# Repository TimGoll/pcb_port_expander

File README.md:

# SPI Port Expander - MCP23S17

library: https://github.com/MajenkoLibraries/MCP23S17

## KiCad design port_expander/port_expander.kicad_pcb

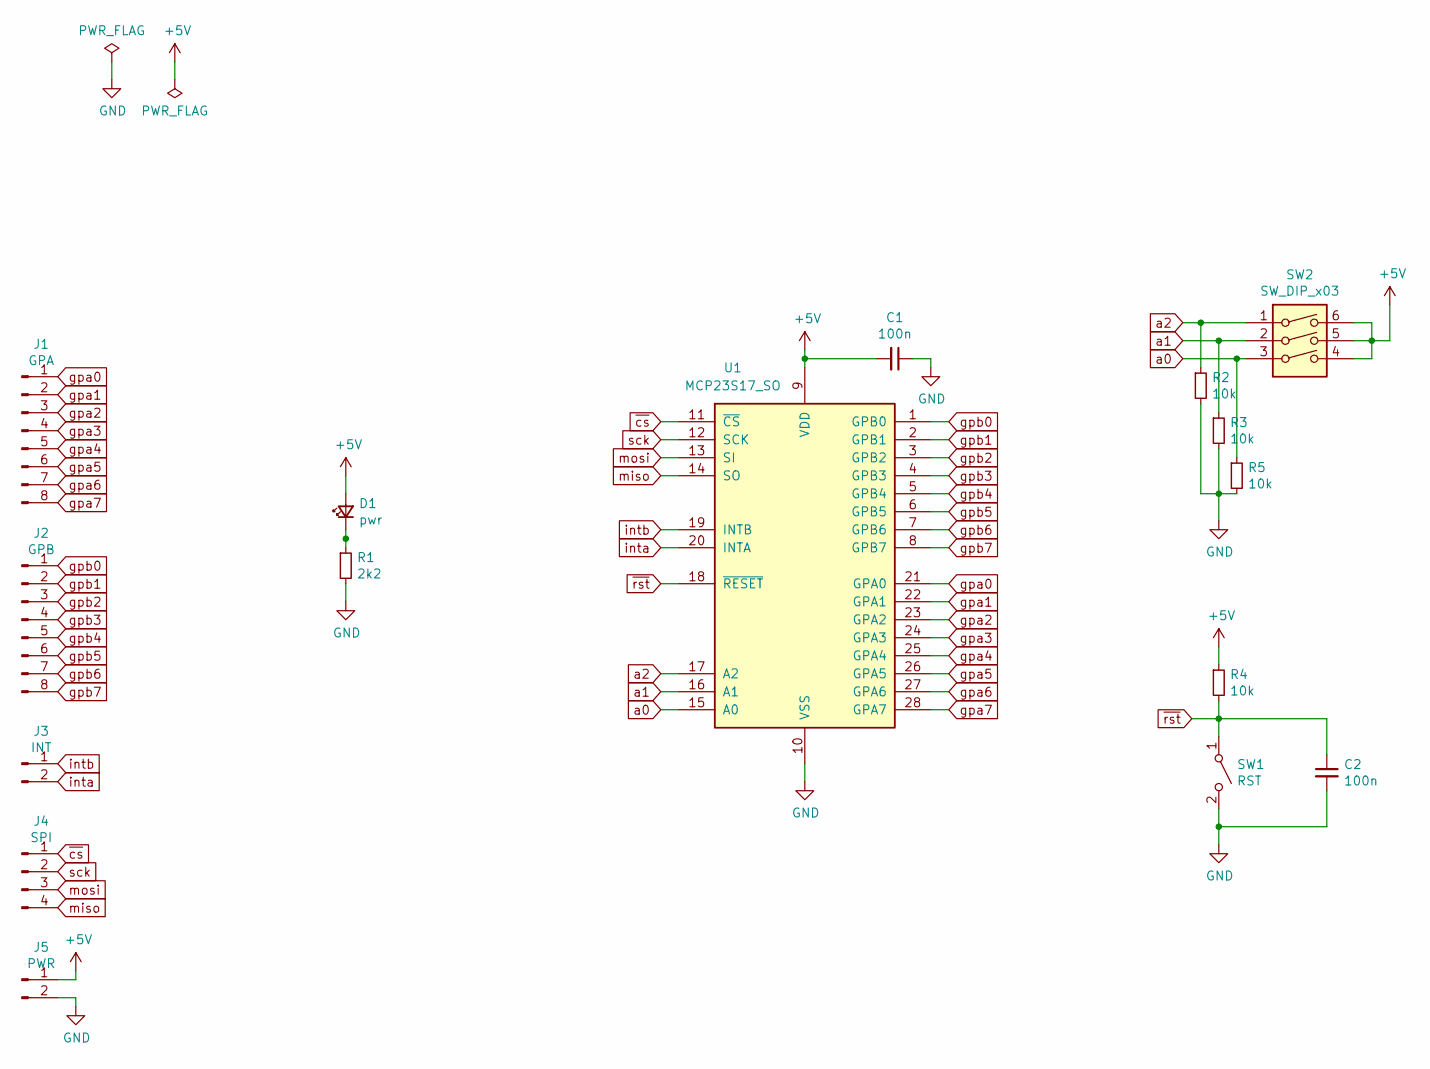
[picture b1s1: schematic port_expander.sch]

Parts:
C1, C2: 100n; C_0805_2012Metric_Pad1.15x1.40mm_HandSolder
D1: pwr; LED_0805_2012Metric_Castellated
J1: GPA; PinHeader_1x08_P2.54mm_Vertical
J2: GPB; PinHeader_1x08_P2.54mm_Vertical
J3: INT; PinHeader_1x02_P2.54mm_Vertical
J4: SPI; PinHeader_1x04_P2.54mm_Vertical
J5: PWR; PinHeader_1x02_P2.54mm_Vertical
R1: 2k2; R_0805_2012Metric_Pad1.15x1.40mm_HandSolder
R2, R3, R4, R5: 10k; R_0805_2012Metric_Pad1.15x1.40mm_HandSolder
SW1: RST; SW_Push_1P1T_NO_6x6mm_H9.5mm
SW2: SW_DIP_x03; DIP-6_W8.89mm_SMDSocket_LongPads
U1: MCP23S17_SO; SOIC-28W_7.5x17.9mm_P1.27mm

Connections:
+5V: C1.2, D1.2 (A), J5.1, R4.1, SW2.4, SW2.5, SW2.6, U1.9 (VDD)
GND: C1.1, C2.2, J5.2, R1.2, R2.2, R3.2, R5.2, SW1.2 (B), U1.10 (VSS); also elsewhere on the board
unnamed: D1.1 (K), R1.1
a0: R5.1, SW2.3, U1.15 (A0)
a1: R3.1, SW2.2, U1.16 (A1)
a2: R2.1, SW2.1, U1.17 (A2)
gpa0: J1.1, U1.21 (GPA0)
gpa1: J1.2, U1.22 (GPA1)
gpa2: J1.3, U1.23 (GPA2)
gpa3: J1.4, U1.24 (GPA3)
gpa4: J1.5, U1.25 (GPA4)
gpa5: J1.6, U1.26 (GPA5)
gpa6: J1.7, U1.27 (GPA6)
gpa7: J1.8, U1.28 (GPA7)
gpb0: J2.1, U1.1 (GPB0)
gpb1: J2.2, U1.2 (GPB1)
gpb2: J2.3, U1.3 (GPB2)
gpb3: J2.4, U1.4 (GPB3)
gpb4: J2.5, U1.5 (GPB4)
gpb5: J2.6, U1.6 (GPB5)
gpb6: J2.7, U1.7 (GPB6)
gpb7: J2.8, U1.8 (GPB7)
inta: J3.2, U1.20 (INTA)
intb: J3.1, U1.19 (INTB)
miso: J4.4, U1.14 (SO)
mosi: J4.3, U1.13 (SI)
sck: J4.2, U1.12 (SCK)
~cs: J4.1, U1.11 (~CS~)
~rst: C2.1, R4.2, SW1.1 (A), U1.18 (~RESET~); also elsewhere on the board

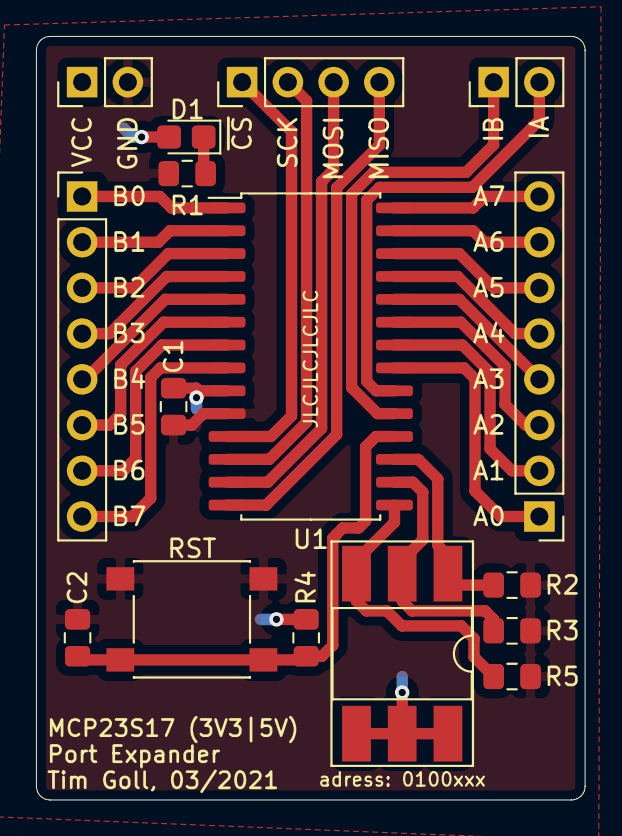
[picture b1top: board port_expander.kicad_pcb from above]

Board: 2 copper layers, 30.5 x 42.4 mm, 16 parts (0 on the bottom side), 29 nets.

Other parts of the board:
RST: RST; SW_Push_1P1T_NO_6x6mm_H9.5mm

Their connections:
GND: RST.2; also elsewhere on the board
~rst: RST.1; also elsewhere on the board

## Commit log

2021-03-11 datasheet
2021-03-12 added schematic and pcb
2021-04-13 pcb update; gerber files
